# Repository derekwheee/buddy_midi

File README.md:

# MIDI Buddy

A breadboard friend for prototyping with MIDI input and output.

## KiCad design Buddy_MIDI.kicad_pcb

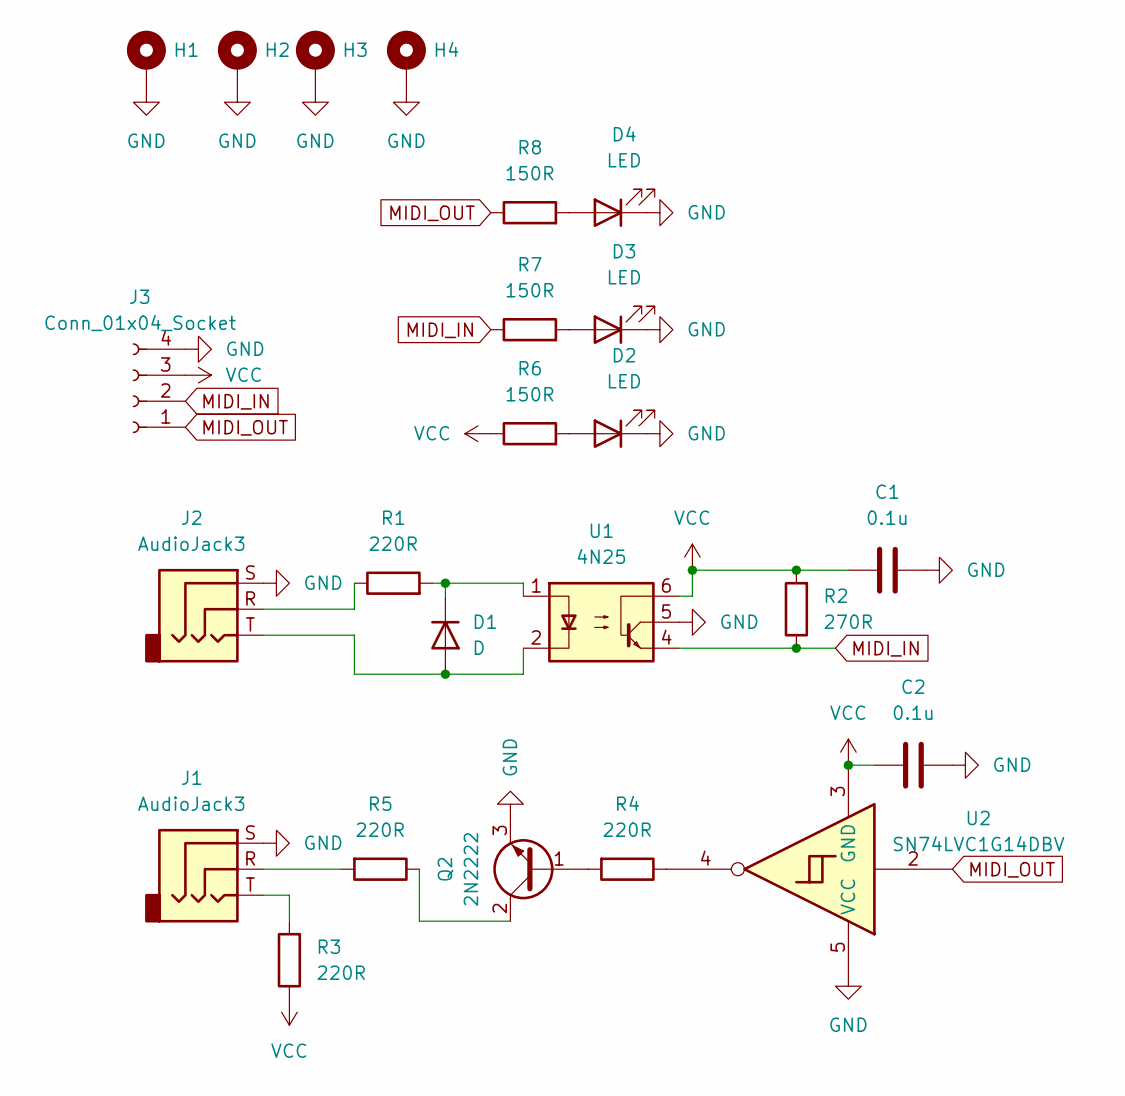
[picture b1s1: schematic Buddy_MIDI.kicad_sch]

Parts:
C1, C2: 0.1u; C_0603_1608Metric; Part # CC0603KRX7R7BB104; LCSC Part # C6666325
D1: D; D_SMA; Part # M7; LCSC Part # C95872
D2: LED; LED_0603_1608Metric; Part # LTST-C190KRKT
D3: LED; LED_0603_1608Metric; Part # LTST-C190GKT
D4: LED; LED_0603_1608Metric; Part # LTST-C190KFKT
H1, H2, H3, H4: MountingHole_Pad; MountingHole_2.2mm_M2_Pad
J1, J2: AudioJack3; Jack_3.5mm_QingPu_WQP-PJ398SM_Vertical_CircularHoles; Part # SJ1-3523N
J3: Conn_01x04_Socket; PinSocket_1x04_P2.54mm_Vertical
Q2: 2N2222; TO-92; Part # 2N2222A; LCSC Part # C21714170
R1, R3, R4, R5: 220R; R_1206_3216Metric; Part # RMCF1206FT220R; LCSC Part # C25336
R2: 270R; R_1206_3216Metric; Part # RMCF1206JT270R; LCSC Part # C50842
R6, R7, R8: 150R; R_1206_3216Metric; Part # RMCF1206JT150R; LCSC Part # C17917
U1: 4N25; DIP-6_W7.62mm; Part # 4N25; LCSC Part # C115480
U2: SN74LVC1G14DBV; SOT-23-5; Part # SN74LVC1G14DBVR; LCSC Part # C434069

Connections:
GND: C1.1, C2.1, D2.1 (K), D3.1 (K), D4.1 (K), H1.1, H2.1, H3.1, H4.1, J1.S, J2.S, J3.4, Q2.3 (E), U1.5, U2.5 (VCC)
MIDI_IN: J3.2, R2.1, R7.1, U1.4
MIDI_OUT: J3.1, R8.1, U2.2
unnamed: D1.2 (A), J2.T, U1.2
unnamed: D1.1 (K), R1.2, U1.1
unnamed: D2.2 (A), R6.2
unnamed: D3.2 (A), R7.2
unnamed: D4.2 (A), R8.2
unnamed: J1.R, R5.2
unnamed: J1.T, R3.2
unnamed: J2.R, R1.1
unnamed: Q2.1 (B), R4.2
unnamed: Q2.2 (C), R5.1
unnamed: R4.1, U2.4
VCC: C1.2, C2.2, J3.3, R2.2, R3.1, R6.1, U1.6, U2.3 (GND)

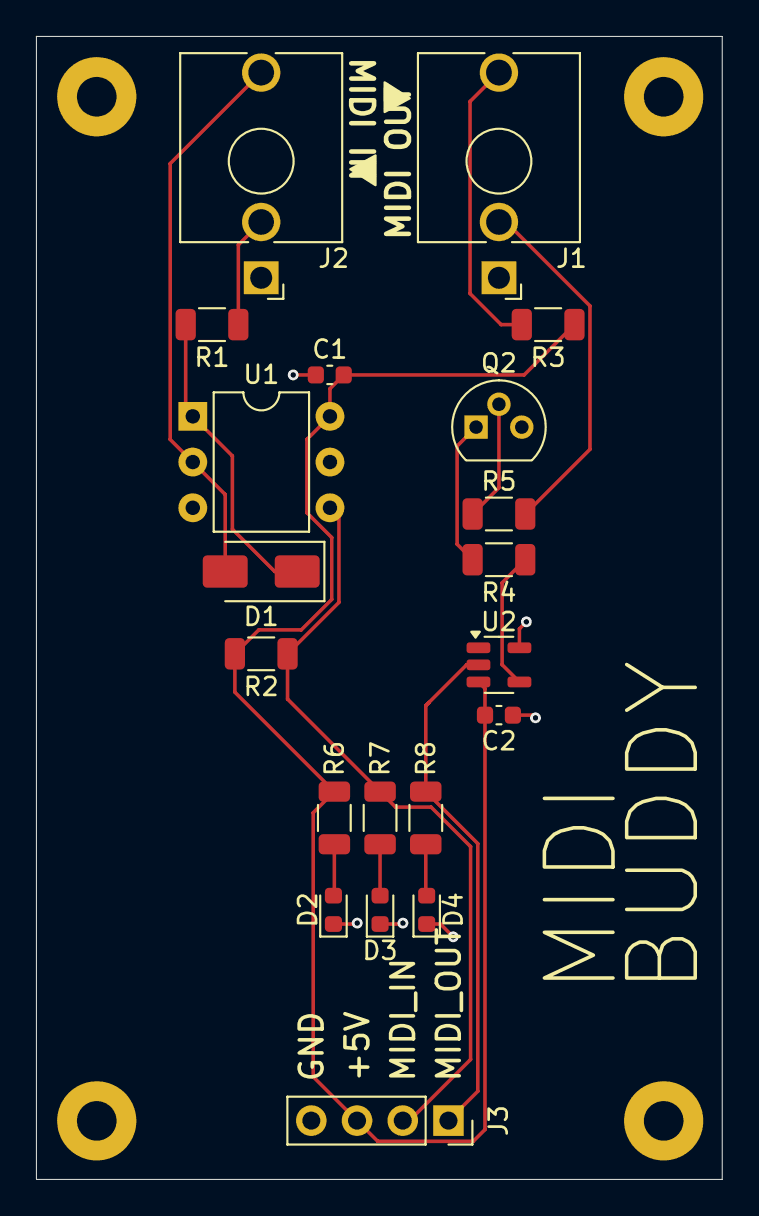
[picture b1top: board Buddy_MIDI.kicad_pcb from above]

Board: 2 copper layers, 38.1 x 63.5 mm, 24 parts (0 on the bottom side), 15 nets.

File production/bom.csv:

Designator,Footprint,Quantity,Value,LCSC Part #
"C1, C2",0603,2,0.1u,C6666325
D1,D_SMA,1,D,C95872
"D2, D3, D4",0603,3,LED,
"J1, J2",Jack_3.5mm_QingPu_WQP-PJ398SM_Vertical_CircularHoles,2,AudioJack3,
Q2,TO-92,1,2N2222,C21714170
"R1, R3, R4, R5",1206,4,220R,C25336
R2,1206,1,270R,C50842
"R6, R7, R8",1206,3,150R,C17917
U1,DIP-6_W7.62mm,1,4N25,C115480
U2,SOT-23-5,1,SN74LVC1G14DBV,C434069

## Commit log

2025-03-06 Remove header from BOM
2025-03-08 New form factor
2025-03-08 Add jack labels
